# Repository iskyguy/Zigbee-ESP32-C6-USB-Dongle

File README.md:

# zigbee-c6-dongle

Board revision: v1.0

A small USB Zigbee coordinator stick built around the Espressif ESP32-C6-MINI-1U-H4 module. It plugs straight into a USB-A port on a Home Assistant host (a Raspberry Pi, for example) and gives it a Zigbee radio with an external antenna connector.

## Purpose

The goal is an open, hand-solderable Zigbee coordinator for Home Assistant that does not depend on a vendor dongle. Every SMD passive is 0603 or larger, all parts are available from DigiKey, and the board is a 4-layer design set up for OSH Park's 4-layer service.

## Hardware

| Item | Detail |
| --- | --- |
| Radio / MCU | ESP32-C6-MINI-1U-H4 (802.15.4 + Wi-Fi 6 + BLE, U.FL antenna connector) |
| USB | Male USB-A plug, ESP32-C6 native USB Serial/JTAG on D+/D- |
| Protection | 500 mA resettable fuse (MF-NSMF050-2) and USBLC6-2SC6 ESD array |
| Power | AP2112K-3.3 3.3 V, 600 mA LDO (pin-compatible with TLV75733P) |
| Expansion | Two 4-pin JST-SH connectors: I2C (Qwiic / STEMMA QT pinout) and UART0 |
| Controls | BOOT and RST buttons, power and status LEDs |
| Board | 58.25 mm x 20.75 mm, 4 layers (signal / GND / 3V3 / signal), 1.6 mm FR408-HR, ENIG, two 2.0 mm case indexing holes |

The board also has an unpopulated footprint for an MCP2221A USB-to-UART bridge. It is a fallback in case the native USB port is not suitable: fit U4 with its support parts and move the two USB series resistors from R3/R4 to R10/R11.

Two normally-open solder jumpers, JP1 and JP2, can also wire the bridge straight to the UART connector so the stick works as a plain 3.3 V USB-to-serial adapter. That mode needs the bridge fitted and the ESP32-C6 held in reset or left unprogrammed.

## Software

The dongle itself runs [esp-coordinator](https://github.com/aliciusschroeder/esp-coordinator), a Zigbee coordinator firmware for the ESP32-C6 that speaks the ZBOSS NCP serial protocol over USB.

On the Home Assistant side there are two options:

- **ZHA** with the [zha-zboss-esp](https://github.com/tostmann/zha-zboss-esp) adapter (installed through HACS). This is the primary target.
- **Zigbee2MQTT** with its `zboss` adapter, as the fallback.

The firmware is flashed over the same USB port. Hold BOOT while tapping RST to enter the ROM bootloader.

## Repository layout

```
hardware/zigbee-c6-dongle/      KiCad project (schematic, PCB, library tables)
hardware/zigbee-c6-dongle/production/   JLCPCB gerbers, BOM and placement files
hardware/zigbee-c6-dongle/production/oshpark/   OSH Park 4-layer gerbers and drill file
documentation/assets/custom/    Project symbol and footprint libraries
documentation/assets/           Vendor CAD downloads and 3D models (STEP)
documentation/datasheet/        Component datasheets
documentation/exports/          PDF plots of the schematic and layout
```

## Opening the project

The project was drawn in KiCad 10. Clone the repository and open `hardware/zigbee-c6-dongle/zigbee-c6-dongle.kicad_pro`. No library setup is needed:

- The `custom` symbol and footprint libraries are registered in the project's own `sym-lib-table` and `fp-lib-table` using `${KIPRJMOD}`-relative paths.
- Vendor 3D models are referenced relative to the project, and the remaining models come from the standard KiCad library (`${KICAD10_3DMODEL_DIR}`).
- Passives, LEDs, switches and the indexing holes use the stock KiCad libraries.

After opening the PCB, press `B` to refill the copper zones before running DRC or exporting fabrication files.

## Ordering from OSH Park

The board's design rules and stackup match OSH Park's 4-layer prototype service, and DRC passes against them. There are two ways to order:

- **Upload the KiCad board.** OSH Park accepts `zigbee-c6-dongle.kicad_pcb` directly and generates the Gerbers itself. It does not refill zones, so press `B` and save before uploading if you have changed anything. The plot settings stored in the board (the layers listed below) are used.
- **Upload the Gerber zip.** `production/oshpark/Zigbee_C6_Dongle_v1.0_OSHPark.zip` holds Gerber X2 files for F.Cu, In1.Cu (`.G2L`), In2.Cu (`.G3L`), B.Cu, both masks, silkscreens and pastes, the Edge.Cuts outline (`.GKO`), a job file, and one Excellon drill file (metric, absolute origin, decimal format, alternate drill mode for the USB plug slots). To regenerate it, use **File > Plot** (the settings are saved in the board and write to `production/oshpark/`) and **Generate Drill Files** with the options above.

Design rules (Board Setup > Constraints), from OSH Park's 4-layer specification:

| Rule | Value |
| --- | --- |
| Minimum clearance, track width and connection width | 0.127 mm (5 mil) |
| Minimum via diameter | 0.4572 mm (18 mil) |
| Minimum annular ring | 0.1016 mm (4 mil) |
| Minimum through hole | 0.254 mm (10 mil) |
| Hole to copper clearance | 0.254 mm (10 mil, OSH Park's plated drill to internal copper limit) |
| Hole to hole clearance | 0.127 mm (5 mil) |
| Copper to board edge | 0.381 mm (15 mil) |
| Solder mask expansion / minimum web | 0.0508 mm (2 mil) / 0.1016 mm (4 mil) |
| Minimum silkscreen text thickness | 0.127 mm (5 mil) |

The routing itself is unchanged and stays well above these limits: 0.2 mm minimum track and clearance, and 0.6 mm vias with 0.3 mm drills. OSH Park offers no blind, buried or via-in-pad vias, and the board uses none.

The stackup in Board Setup follows OSH Park's published 4-layer build: 1 oz outer copper (0.0432 mm), 0.1999 mm FR408-HR 2113 prepreg, 0.5 oz inner copper (0.0175 mm), and a 0.9906 mm FR408-HR core, with Dk 3.61, ENIG finish, purple mask and white silkscreen. OSH Park quotes the finished board as 1.6 mm nominal. These values only matter for impedance calculations, since OSH Park always builds to its own stackup.

At OSH Park's $10 per square inch the 58.25 mm x 20.75 mm board is about 1.87 square inches, so a set of three costs about $19.

## Third-party files

The vendor symbols, footprints and STEP models under `documentation/assets/` belong to their respective manufacturers and CAD providers. Licence notes are kept alongside the files where the source supplied them.

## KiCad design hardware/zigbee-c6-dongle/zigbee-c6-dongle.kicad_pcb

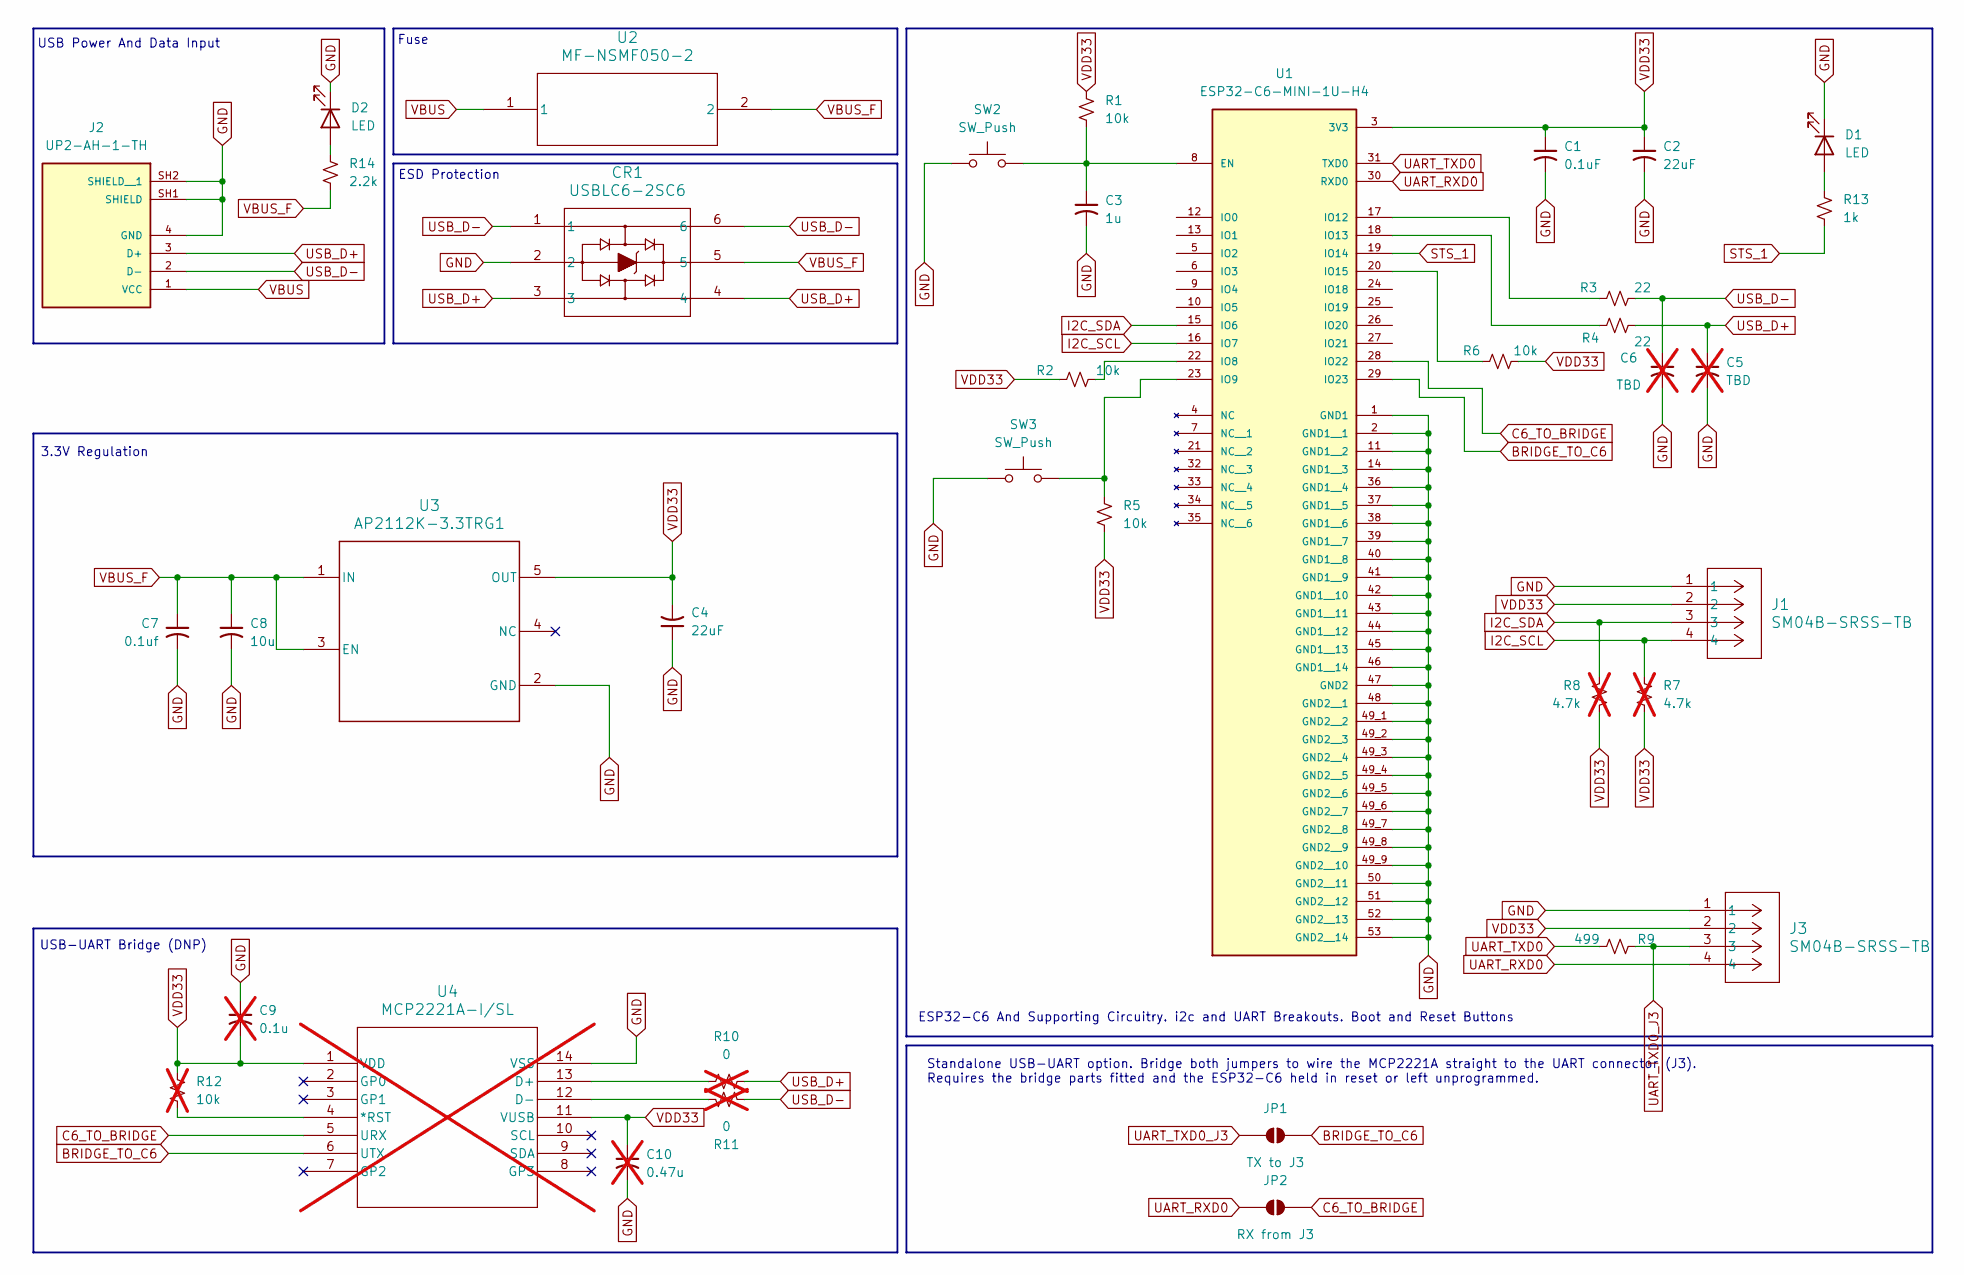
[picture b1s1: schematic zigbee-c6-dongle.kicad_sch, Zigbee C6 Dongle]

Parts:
C1: 0.1uF; C_0603_1608Metric_Pad1.08x0.95mm_HandSolder
C2, C4: 22uF; C_0805_2012Metric_Pad1.18x1.45mm_HandSolder
C3: 1u; C_0603_1608Metric_Pad1.08x0.95mm_HandSolder
C5, C6: TBD; C_0603_1608Metric_Pad1.08x0.95mm_HandSolder; not fitted
C7: 0.1uf; C_0603_1608Metric_Pad1.08x0.95mm_HandSolder
C8: 10u; C_0805_2012Metric_Pad1.18x1.45mm_HandSolder
C9: 0.1u; C_0603_1608Metric_Pad1.08x0.95mm_HandSolder; not fitted
C10: 0.47u; C_0603_1608Metric_Pad1.08x0.95mm_HandSolder; not fitted
CR1: USBLC6-2SC6; SOT23-6L_STM-M
D1, D2: LED; LED_0603_1608Metric_Pad1.05x0.95mm_HandSolder
J1, J3: SM04B-SRSS-TB; CONN_SM04B-SRSS-TB_JST
J2: UP2-AH-1-TH; CUI_UP2-AH-1-TH; MPN UP2-AH-1-TH
JP1: TX to J3; SolderJumper-2_P1.3mm_Open_Pad1.0x1.5mm
JP2: RX from J3; SolderJumper-2_P1.3mm_Open_Pad1.0x1.5mm
R1, R2, R5, R6: 10k; R_0603_1608Metric_Pad0.98x0.95mm_HandSolder
R3, R4: 22; R_0603_1608Metric_Pad0.98x0.95mm_HandSolder
R7, R8: 4.7k; R_0603_1608Metric_Pad0.98x0.95mm_HandSolder; not fitted
R9: 499; R_0603_1608Metric_Pad0.98x0.95mm_HandSolder
R10, R11: 0; R_0603_1608Metric_Pad0.98x0.95mm_HandSolder; not fitted
R12: 10k; R_0603_1608Metric_Pad0.98x0.95mm_HandSolder; not fitted
R13: 1k; R_0603_1608Metric_Pad0.98x0.95mm_HandSolder
R14: 2.2k; R_0603_1608Metric_Pad0.98x0.95mm_HandSolder
SW2, SW3: SW_Push; PTS526-G15_CNK
U1: ESP32-C6-MINI-1U-H4; XCVR_ESP32-C6-MINI-1U-H4; MPN ESP32-C6-MINI-1U-H4
U2: MF-NSMF050-2; CHIP_NSMF050_3P4XP18-M
U3: AP2112K-3.3TRG1; DBV0005A_M
U4: MCP2221A-I/SL; SOIC14_SL_MCH-M; not fitted

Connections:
BRIDGE_TO_C6: JP1.2 (B), U1.29 (IO23), U4.6 (UTX)
C6_TO_BRIDGE: JP2.2 (B), U1.28 (IO22), U4.5 (URX)
GND: C1.2, C2.2, C3.2, C4.1, C5.2, C6.2, C7.2, C8.2, C9.1, C10.2, CR1.2, D1.1 (K), D2.1 (K), J1.1, J2.4 (GND), J2.SH1 (SHIELD), J2.SH2 (SHIELD__1), J3.1, SW2.1, SW3.2, U1.1 (GND1), U1.2 (GND1__1), U1.11 (GND1__2), U1.14 (GND1__3), U1.36 (GND1__4), U1.37 (GND1__5), U1.38 (GND1__6), U1.39 (GND1__7), U1.40 (GND1__8), U1.41 (GND1__9), U1.42 (GND1__10), U1.43 (GND1__11), U1.44 (GND1__12), U1.45 (GND1__13), U1.46 (GND1__14), U1.47 (GND2), U1.48 (GND2__1), U1.49_1 (GND2__2), U1.49_2 (GND2__3), U1.49_3 (GND2__4), U1.49_4 (GND2__5), U1.49_5 (GND2__6), U1.49_6 (GND2__7), U1.49_7 (GND2__8), U1.49_8 (GND2__9), U1.49_9 (GND2__10), U1.50 (GND2__11), U1.51 (GND2__12), U1.52 (GND2__13), U1.53 (GND2__14), U3.2 (GND), U4.14 (VSS)
I2C_SCL: J1.4, R7.1, U1.16 (IO7)
I2C_SDA: J1.3, R8.1, U1.15 (IO6)
unnamed: D1.2 (A), R13.1
unnamed: D2.2 (A), R14.1
unnamed: C3.1, R1.2, SW2.2, U1.8 (EN)
unnamed: R2.2, U1.22 (IO8)
unnamed: R5.2, SW3.1, U1.23 (IO9)
unnamed: R3.1, U1.17 (IO12)
unnamed: R4.1, U1.18 (IO13)
unnamed: R6.1, U1.20 (IO15)
unnamed: R12.1, U4.4 (*RST)
unnamed: R10.1, U4.13 (D+)
unnamed: R11.1, U4.12 (D-)
STS_1: R13.2, U1.19 (IO14)
UART_RXD0: J3.4, JP2.1 (A), U1.30 (RXD0)
UART_TXD0: R9.2, U1.31 (TXD0)
UART_TXD0_J3: J3.3, JP1.1 (A), R9.1
USB_D+: C5.1, CR1.3, CR1.4, J2.3 (D+), R4.2, R10.2
USB_D-: C6.1, CR1.1, CR1.6, J2.2 (D-), R3.2, R11.2
VBUS: J2.1 (VCC), U2.1
VBUS_F: C7.1, C8.1, CR1.5, R14.2, U2.2, U3.1 (IN), U3.3 (EN)
VDD33: C1.1, C2.1, C4.2, C9.2, C10.1, J1.2, J3.2, R1.1, R2.1, R5.1, R6.2, R7.2, R8.2, R12.2, U1.3 (3V3), U3.5 (OUT), U4.1 (VDD), U4.11 (VUSB)

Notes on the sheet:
ESD Protection
Fuse
ESP32-C6 And Supporting Circuitry. i2c and UART Breakouts. Boot and Reset Buttons
USB Power And Data Input
USB-UART Bridge (DNP)
3.3V Regulation
Standalone USB-UART option. Bridge both jumpers to wire the MCP2221A straight to the UART connector (J3). Requires the bridge parts fitted and the ESP32-C6 held in reset or left unprogrammed.

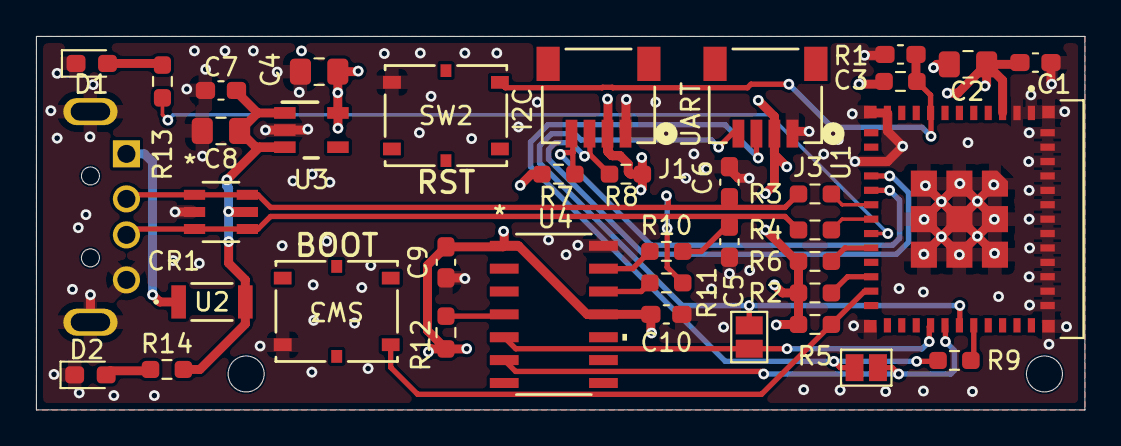
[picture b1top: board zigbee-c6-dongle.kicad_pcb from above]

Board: 4 copper layers, 58.2 x 20.8 mm, 40 parts (1 on the bottom side), 25 nets.

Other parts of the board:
H1, H2: IndexHole_2mm; MountingHole_2mm

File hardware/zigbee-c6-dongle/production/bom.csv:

Designator,Footprint,Quantity,Value,LCSC Part #
"C1, C7",0603,2,0.1uF,
C10,0603,1,0.47u,
"C2, C4",0805,2,22uF,
C3,0603,1,1u,
"C5, C6",0603,2,TBD,
C8,0805,1,10u,
C9,0603,1,0.1u,
CR1,SOT23-6L_STM-M,1,USBLC6-2SC6,
"D1, D2",0603,2,LED,
"J1, J3",CONN_SM04B-SRSS-TB_JST,2,SM04B-SRSS-TB,
J2,CUI_UP2-AH-1-TH,1,UP2-AH-1-TH,UP2-AH-1-TH
"R1, R12, R2, R5, R6",0603,5,10k,
"R10, R11",0603,2,0,
R13,0603,1,1k,
R14,0603,1,2.2k,
"R3, R4",0603,2,22,
"R7, R8",0603,2,4.7k,
R9,0603,1,499,
"SW2, SW3",PTS526-G15_CNK,2,SW_Push,
U1,XCVR_ESP32-C6-MINI-1U-H4,1,ESP32-C6-MINI-1U-H4,ESP32-C6-MINI-1U-H4
U2,CHIP_NSMF050_3P4XP18-M,1,MF-NSMF050-2,
U3,DBV0005A_M,1,AP2112K-3.3TRG1,
U4,SOIC14_SL_MCH-M,1,MCP2221A-I/SL,
